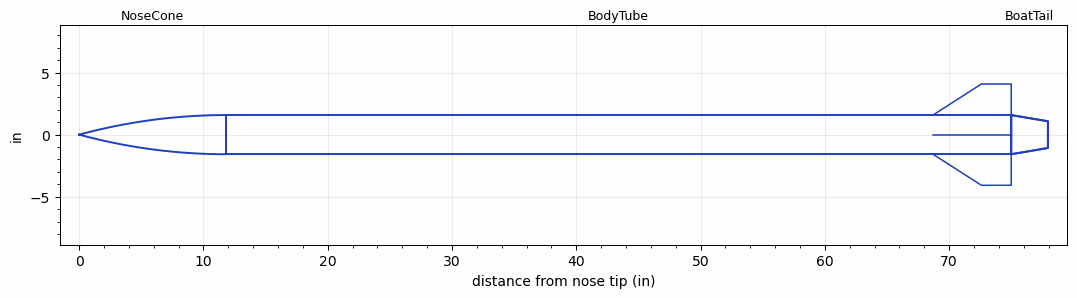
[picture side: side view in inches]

<RASAeroDocument>
 <FileVersion>2</FileVersion>
 <RocketDesign>
  <NoseCone>
   <Length>11.81</Length>
   <Diameter>3.15</Diameter>
   <Shape>Tangent Ogive</Shape>
   <Location>0</Location>
  </NoseCone>
  <BodyTube>
   <Length>63.19</Length>
   <Diameter>3.15</Diameter>
   <RailGuideDiameter>0.2</RailGuideDiameter>
   <RailGuideHeight>0.2</RailGuideHeight>
   <Location>11.81</Location>
   <BoattailLength>2.95</BoattailLength>
   <BoattailRearDiameter>2.15</BoattailRearDiameter>
   <Fin>
    <Count>4</Count>
    <Chord>6.3</Chord>
    <Span>2.5</Span>
    <SweepDistance>3.9</SweepDistance>
    <TipChord>2.4</TipChord>
    <Thickness>0.12</Thickness>
    <LERadius>0.04</LERadius>
    <Location>6.3</Location>
    <AirfoilSection>Hexagonal</AirfoilSection>
    <FX1>0.12</FX1>
    <FX3>0.12</FX3>
   </Fin>
  </BodyTube>
  <BoatTail>
   <Length>2.95</Length>
   <Diameter>3.15</Diameter>
   <RearDiameter>2.15</RearDiameter>
   <Location>75</Location>
  </BoatTail>
  <Surface>Smooth Paint</Surface>
  <ModifiedBarrowman>False</ModifiedBarrowman>
  <Turbulence>False</Turbulence>
  <SustainerNozzle>2.1</SustainerNozzle>
  <UseBooster1>False</UseBooster1>
  <UseBooster2>False</UseBooster2>
 </RocketDesign>
 <LaunchSite>
  <Altitude>0</Altitude>
  <Pressure>0</Pressure>
  <RodAngle>0</RodAngle>
  <RodLength>4</RodLength>
  <Temperature>74</Temperature>
  <WindSpeed>7</WindSpeed>
 </LaunchSite>
 <Recovery>
  <Altitude1>1000</Altitude1>
  <Altitude2>1000</Altitude2>
  <DeviceType1>None</DeviceType1>
  <DeviceType2>None</DeviceType2>
  <Event1>False</Event1>
  <Event2>False</Event2>
  <Size1>1</Size1>
  <Size2>1</Size2>
  <EventType1>None</EventType1>
  <EventType2>None</EventType2>
  <CD1>1.33</CD1>
  <CD2>1.33</CD2>
 </Recovery>
 <SimulationList>
  <Simulation>
   <SustainerEngine>K1440  (CTI)</SustainerEngine>
   <SustainerLaunchWt>13.85</SustainerLaunchWt>
   <SustainerNozzleDiameter>2.13</SustainerNozzleDiameter>
   <SustainerCG>44.88</SustainerCG>
   <SustainerIgnitionDelay>0</SustainerIgnitionDelay>
   <Booster1SeparationDelay>0</Booster1SeparationDelay>
   <Booster1IgnitionDelay>0</Booster1IgnitionDelay>
   <IncludeBooster1>False</IncludeBooster1>
   <Booster2Delay>0</Booster2Delay>
   <IncludeBooster2>False</IncludeBooster2>
   <TimetoApogee>25.12048</TimetoApogee>
   <MaxAltitude>12073.03</MaxAltitude>
   <MaxVelocity>1244.628</MaxVelocity>
   <OptimumWt>10.04125</OptimumWt>
   <OptimumMaxAlt>10.04125</OptimumMaxAlt>
  </Simulation>
 </SimulationList>
</RASAeroDocument>
